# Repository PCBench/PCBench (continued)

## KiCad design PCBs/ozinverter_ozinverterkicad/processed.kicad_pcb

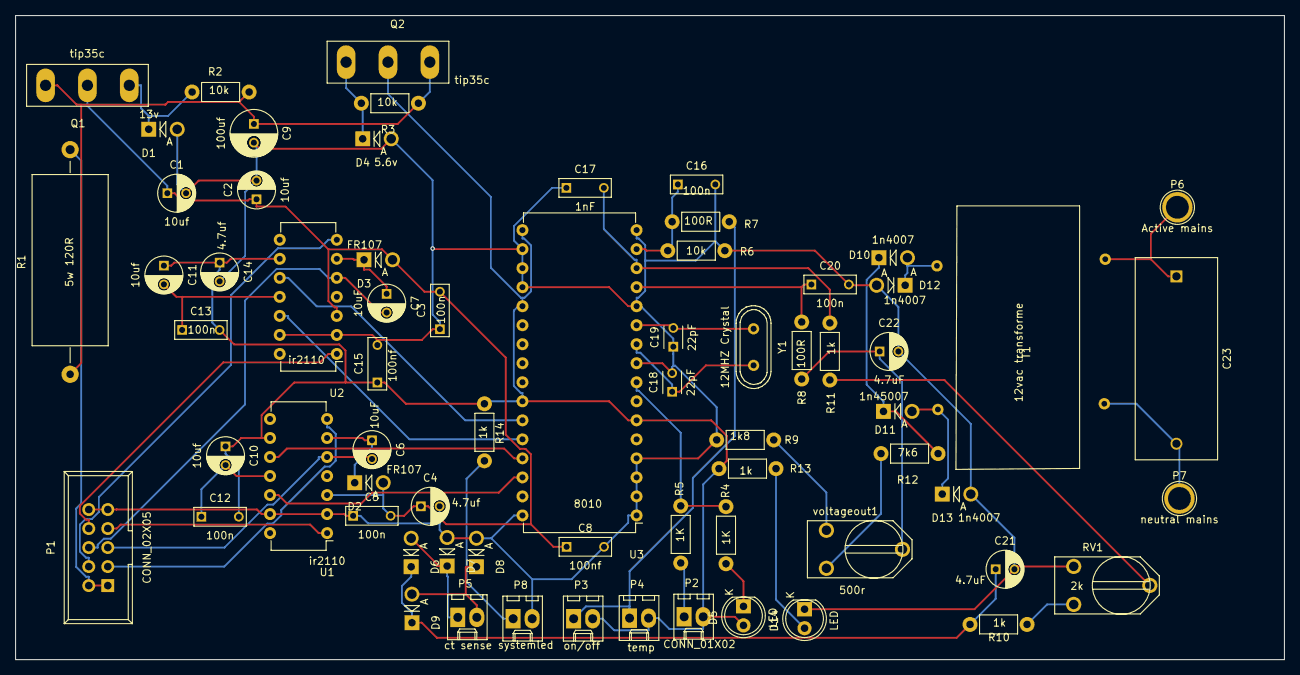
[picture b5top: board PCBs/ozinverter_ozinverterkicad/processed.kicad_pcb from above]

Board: 2 copper layers, 169.4 x 86.0 mm, 68 parts (0 on the bottom side), 45 nets.

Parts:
C1, C2: 10uf; C_Radial_D5_L6_P2.5
C3, C5, C12, C13, C16, C20: 100n; C_Rect_L7_W2.5_P5
C4, C14: 4.7uf; C_Radial_D5_L6_P2.5
C6, C7: 10uF; C_Radial_D5_L6_P2.5
C8, C15: 100nf; C_Rect_L7_W2.5_P5
C9: 100uf; C_Radial_D6.3_L11.2_P2.5
C10, C11: 10uf; C_Radial_D5_L11_P2.5
C17: 1nF; C_Rect_L7_W2.5_P5
C18, C19: 22pF; C_Disc_D3_P2.5
C21, C22: 4.7uF; C_Radial_D5_L6_P2.5
C23: 2uf; C_Rect_L27_W11_P22
D1: 13v; Diode_DO-41_SOD81_Vertical_AnodeUp
D2, D3: FR107; Diode_DO-41_SOD81_Vertical_AnodeUp
D4: 5.6v; Diode_DO-41_SOD81_Vertical_AnodeUp
D5, D14: LED; LED-5MM
D6, D7, D8, D9: D; Diode_DO-41_SOD81_Vertical_AnodeUp
D10, D12, D13: 1n4007; Diode_DO-41_SOD81_Vertical_AnodeUp
D11: 1n45007; Diode_DO-41_SOD81_Vertical_AnodeUp
P1: CONN_02X05; IDC_Header_Straight_10pins
P2: CONN_01X02; Molex_KK-6410-02_02x2.54mm_Straight
P3: on/off; Molex_KK-6410-02_02x2.54mm_Straight
P4: temp; Molex_KK-6410-02_02x2.54mm_Straight
P5: ct sense; Molex_KK-6410-02_02x2.54mm_Straight
P6: Active mains; 1pin
P7: neutral mains; 1pin
P8: systemled; Molex_KK-6410-02_02x2.54mm_Straight
Q1, Q2: tip35c; TO-247_Vertical_Neutral123
R1: 5w 120R; Resistor_Horizontal_RM30mm
R2, R3, R6: 10k; Resistor_Horizontal_RM7mm
R4, R5: 1K; Resistor_Horizontal_RM7mm
R7, R11: 100R; Resistor_Horizontal_RM7mm
R8, R10, R13, R14: 1k; Resistor_Horizontal_RM7mm
R9: 1k8; Resistor_Horizontal_RM7mm
R12: 7k6; Resistor_Horizontal_RM7mm
RV1: 2k; RV2X4
T1: 12vac transforme; 3wtransformer
U1, U2: ir2110; DIP-14_W7.62mm
U3: 8010; DIP-32_W15.24mm
Y1: 12MHZ Crystal; Crystal_HC49-U_Vertical
voltageout1: 500r; RV2X4

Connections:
+5V: C10.1, C11.1, C12.2, C13.2, C14.1, C15.1, D5.2, P2.2, P3.2, P4.2, Q2.2, R13.1, R14.1, U1.9, U2.9, U3.6, U3.17, U3.21, U3.26
+12V: C1.1, C2.1, C3.2, C4.1, C5.2, C8.1, D2.2, D3.2, Q1.2, U1.3, U2.3
+48V: P1.1, P1.2, R1.2
/24vin: C9.1, Q1.3, Q2.3, R1.1, R2.1, R3.1
GND: C1.2, C2.2, C3.1, C4.2, C5.1, C8.2, C9.2, C14.2, C15.2, C16.2, C17.1, C18.2, C19.1, C20.2, C21.2, C22.2, D1.2, D4.2, D7.2, D8.2, D12.2, D13.2, D14.1, P1.9, P1.10, P8.2, R6.2, R9.1, RV1.1, U1.2, U1.13, U2.2, U2.13, U3.1, U3.2, U3.3, U3.4, U3.9, U3.12, U3.16, U3.18, U3.19, U3.20, U3.32
unnamed: C6.1, D2.1, U1.6
unnamed: C6.2, P1.5, U1.5
unnamed: C7.1, D3.1, U2.6
unnamed: C7.2, P1.6, U2.5
unnamed: C10.2, C12.1, U1.11
unnamed: C11.2, C13.1, U2.11
unnamed: C16.1, R6.1, R7.2, U3.15
unnamed: C17.2, R8.2, U3.14
unnamed: C18.1, U3.10, Y1.2
unnamed: C19.2, U3.11, Y1.1
unnamed: C20.1, R11.1, U3.13
unnamed: C21.1, D6.1, D9.1, R10.1
unnamed: C22.1, R11.2, voltageout1.2
unnamed: C23.1, P6.1, T1.4
unnamed: C23.2, P7.1, T1.3
unnamed: D1.1, Q1.1, R2.2
unnamed: D4.1, Q2.1, R3.2
unnamed: D5.1, R4.2
unnamed: D6.2, D7.1, P5.1
unnamed: D8.1, D9.2, P5.2
unnamed: D10.1, D11.1, R12.1
unnamed: D10.2, D12.1, T1.2
unnamed: D11.2, D13.1, T1.1
unnamed: D14.2, R13.2
unnamed: P1.3, U1.7
unnamed: P1.4, U2.7
unnamed: P1.7, U1.1
unnamed: P1.8, U2.1
unnamed: P2.1, R5.2
unnamed: P3.1, P4.1, R7.1
unnamed: P8.1, R14.2
unnamed: R4.1, R5.1, U3.8
unnamed: R8.1, RV1.2
unnamed: R9.2, voltageout1.1
unnamed: R10.2, RV1.3
unnamed: R12.2, voltageout1.3
unnamed: U1.10, U3.29
unnamed: U1.12, U3.30
unnamed: U2.10, U3.27
unnamed: U2.12, U3.28

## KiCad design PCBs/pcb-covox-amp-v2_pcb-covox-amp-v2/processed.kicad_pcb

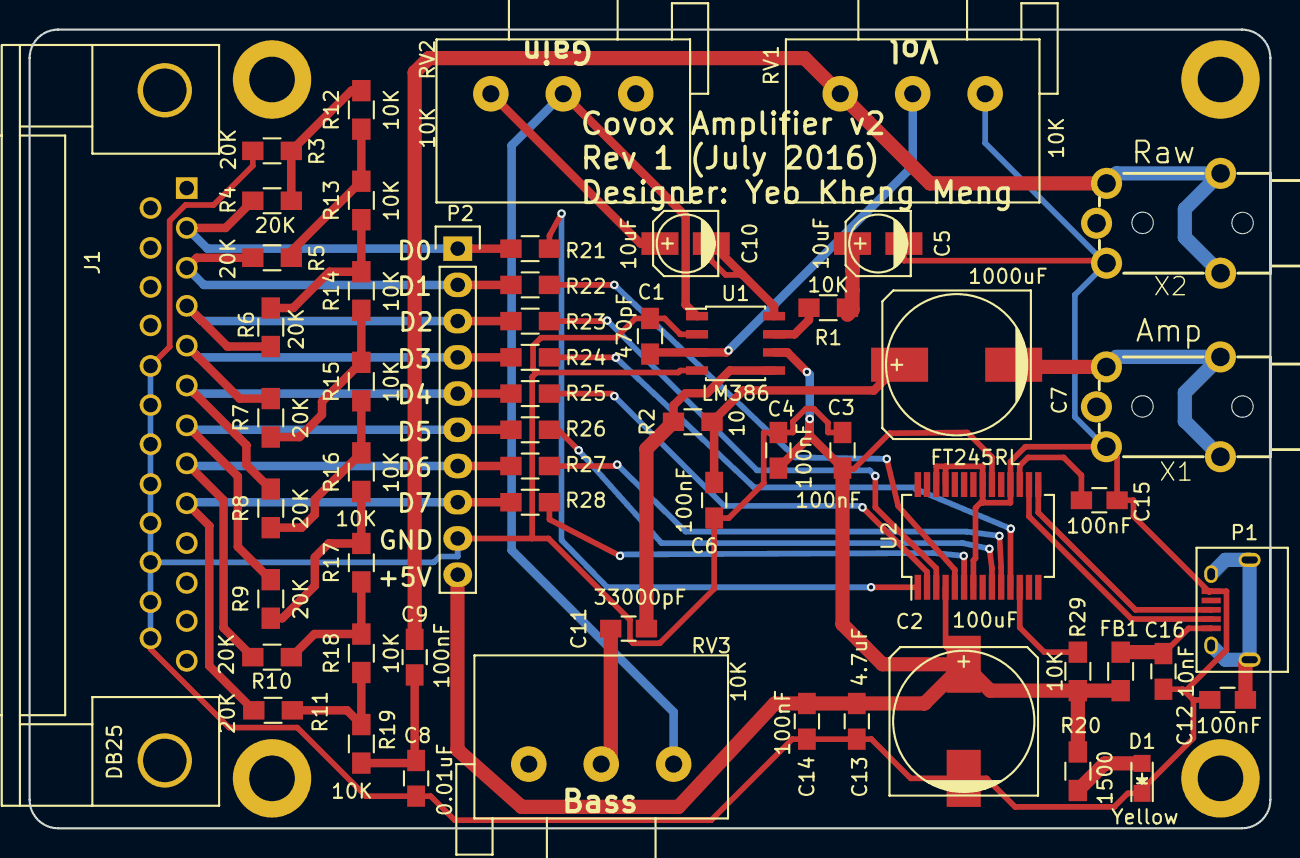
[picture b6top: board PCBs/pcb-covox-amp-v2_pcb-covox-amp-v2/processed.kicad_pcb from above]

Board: 2 copper layers, 87.0 x 56.0 mm, 61 parts (0 on the bottom side), 45 nets.

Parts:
C1: 470pF; C_0805_HandSoldering
C2: 100uF; c_elec_10x10.5
C3, C4, C6, C9, C12, C14, C15: 100nF; C_0805_HandSoldering
C5, C10: 10uF; c_elec_4x5.3
C7: 1000uF; c_elec_10x10.5
C8: 0.01uF; C_0805_HandSoldering
C11: 33000pF; C_0805_HandSoldering
C13: 4.7uF; C_0805_HandSoldering
C16: 10nF; C_0805_HandSoldering
D1: Yellow; LED_0805
FB1: FERRITE; R_0805_HandSoldering
J1: DB25; DB25MC
MH1, MH2, MH3, MH4: MOUNTHOLE; MountingHole_3.2mm_M3_ISO14580_Pad
P1: USB; USB_Micro-B
P2: CONN_01X10; Pin_Header_Straight_1x10
R1, R12, R13, R14, R15, R16, R17, R18, R19, R29: 10K; R_0805_HandSoldering
R2: 10; R_0805_HandSoldering
R3, R4, R5, R6, R7, R8, R9, R10, R11: 20K; R_0805_HandSoldering
R20: 1500; R_0805_HandSoldering
R21, R22, R23, R24, R25, R26, R27, R28: 100; R_0805_HandSoldering
RV1, RV2, RV3: 10K; Potentiometer_Alps-RK163-single_15mm
U1: LM386; SOIC-8_3.9x4.9mm_Pitch1.27mm
U2: FT245RL; SSOP-28_5.3x10.2mm_Pitch0.65mm
X1: Amp; mj-2135-MJ-2135
X2: Raw; mj-2135-MJ-2135

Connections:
+5V: C2.1, C3.1, C4.1, C13.1, C14.1, FB1.2, P2.10, R20.1, R29.1, U1.6, U2.4, U2.20
Amp-Audio: C7.2, X1.P$3, X1.P$4, X1.P$5
Data0: J1.2, P2.1, R4.2, R21.1
Data1: J1.3, P2.2, R5.2, R22.1
Data2: J1.4, P2.3, R6.2, R23.1
Data3: J1.5, P2.4, R7.2, R24.1
Data4: J1.6, P2.5, R8.2, R25.1
Data5: J1.7, P2.6, R9.2, R26.1
Data6: J1.8, P2.7, R10.2, R27.1
Data7: J1.9, P2.8, R11.2, R28.1
GND: C1.1, C2.2, C3.2, C4.2, C5.2, C6.2, C8.2, C12.1, C13.2, C14.2, C15.2, C16.2, D1.1, J1.18, J1.19, J1.20, J1.21, J1.22, J1.23, J1.24, J1.25, P1.5, P2.9, R3.2, RV1.1, U1.2, U1.4, U2.7, U2.18, U2.21, U2.25, U2.26, X1.P$2, X2.P$2
Gain1: RV2.2, RV3.3, U1.1
Gain8: C10.2, U1.8
Input+: C1.2, RV1.2, U1.3
unnamed: C5.1, R1.1
unnamed: C6.1, C7.1, R2.1
unnamed: C8.1, C9.1, R19.1
unnamed: C10.1, RV2.3
unnamed: C11.2, RV3.2
unnamed: C12.2, P1.6
unnamed: C15.1, U2.17
unnamed: C16.1, FB1.1, P1.1
unnamed: D1.2, R20.2
unnamed: R1.2, U1.7
unnamed: R10.1, R17.1, R18.2
unnamed: R11.1, R18.1, R19.2
unnamed: R5.1, R12.1, R13.2
unnamed: R3.1, R4.1, R12.2
unnamed: R6.1, R13.1, R14.2
unnamed: R7.1, R14.1, R15.2
unnamed: R8.1, R15.1, R16.2
unnamed: R9.1, R16.1, R17.2
unnamed: R21.2, U2.1
unnamed: R22.2, U2.5
unnamed: R23.2, U2.3
unnamed: R24.2, U2.11
unnamed: R25.2, U2.2
unnamed: R26.2, U2.9
unnamed: R27.2, U2.10
unnamed: R28.2, U2.6
unnamed: R29.2, U2.12
Source-Audio: C9.2, RV1.3, X2.P$3, X2.P$4, X2.P$5
USB_D+: P1.3, U2.15
USB_D-: P1.2, U2.16
Vout: C11.1, R2.2, U1.5

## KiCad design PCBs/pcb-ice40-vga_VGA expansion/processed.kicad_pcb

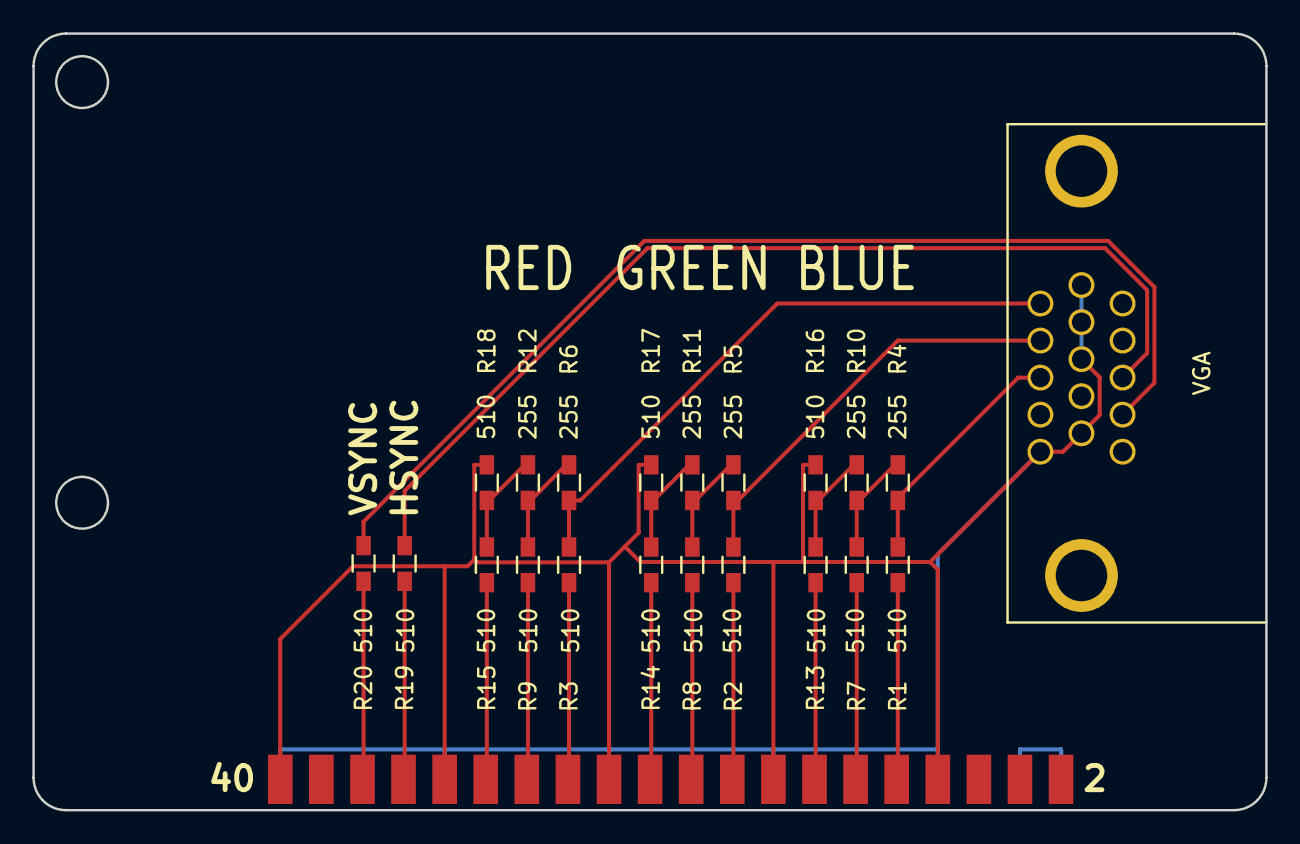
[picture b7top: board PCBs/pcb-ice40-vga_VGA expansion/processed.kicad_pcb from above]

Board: 2 copper layers, 76.2 x 48.0 mm, 22 parts (0 on the bottom side), 24 nets.

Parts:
P1: VGA; VGA_Connector
P2: CONN_02X20; 20x2_EdgePinHeaders
R1, R2, R3, R7, R8, R9, R13, R14, R15, R16, R17, R18, R19, R20: 510; R_0603_HandSoldering
R4, R5, R6, R10, R11, R12: 255; R_0603_HandSoldering

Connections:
+1V2: P2.1, P2.3
BLUE: P1.3, R1.1, R4.1
GND: P1.5, P1.6, P1.7, P1.8, P1.10, P2.7, P2.8, P2.15, P2.16, P2.23, P2.24, P2.31, P2.32, P2.39, P2.40, R16.2, R17.2, R18.2
GREEN: P1.2, R2.1, R5.1
HSYNC: P1.13, R19.1
unnamed: P2.10, R1.2
unnamed: P2.12, R7.2
unnamed: P2.14, R13.2
unnamed: P2.18, R2.2
unnamed: P2.20, R8.2
unnamed: P2.22, R14.2
unnamed: P2.26, R3.2
unnamed: P2.28, R9.2
unnamed: P2.30, R15.2
unnamed: P2.34, R19.2
unnamed: P2.36, R20.2
unnamed: R4.2, R7.1, R10.1
unnamed: R10.2, R13.1, R16.1
unnamed: R5.2, R8.1, R11.1
unnamed: R11.2, R14.1, R17.1
unnamed: R6.2, R9.1, R12.1
unnamed: R12.2, R15.1, R18.1
RED: P1.1, R3.1, R6.1
VSYNC: P1.14, R20.1
